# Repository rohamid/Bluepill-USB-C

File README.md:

# STM32F103 Bluepill USB C #
STM32F103 Bluepill PCB with USB C and castellated PCB.

## Warning ##
After finished and ordering from `JLCPCB` I spotted a mistake that I swapped USB D- with D+ and vice versa.

## Problem fixed ##
* [ ] Fixing swapped D- D+ USB trace

## Bluepill USB C PCB ##

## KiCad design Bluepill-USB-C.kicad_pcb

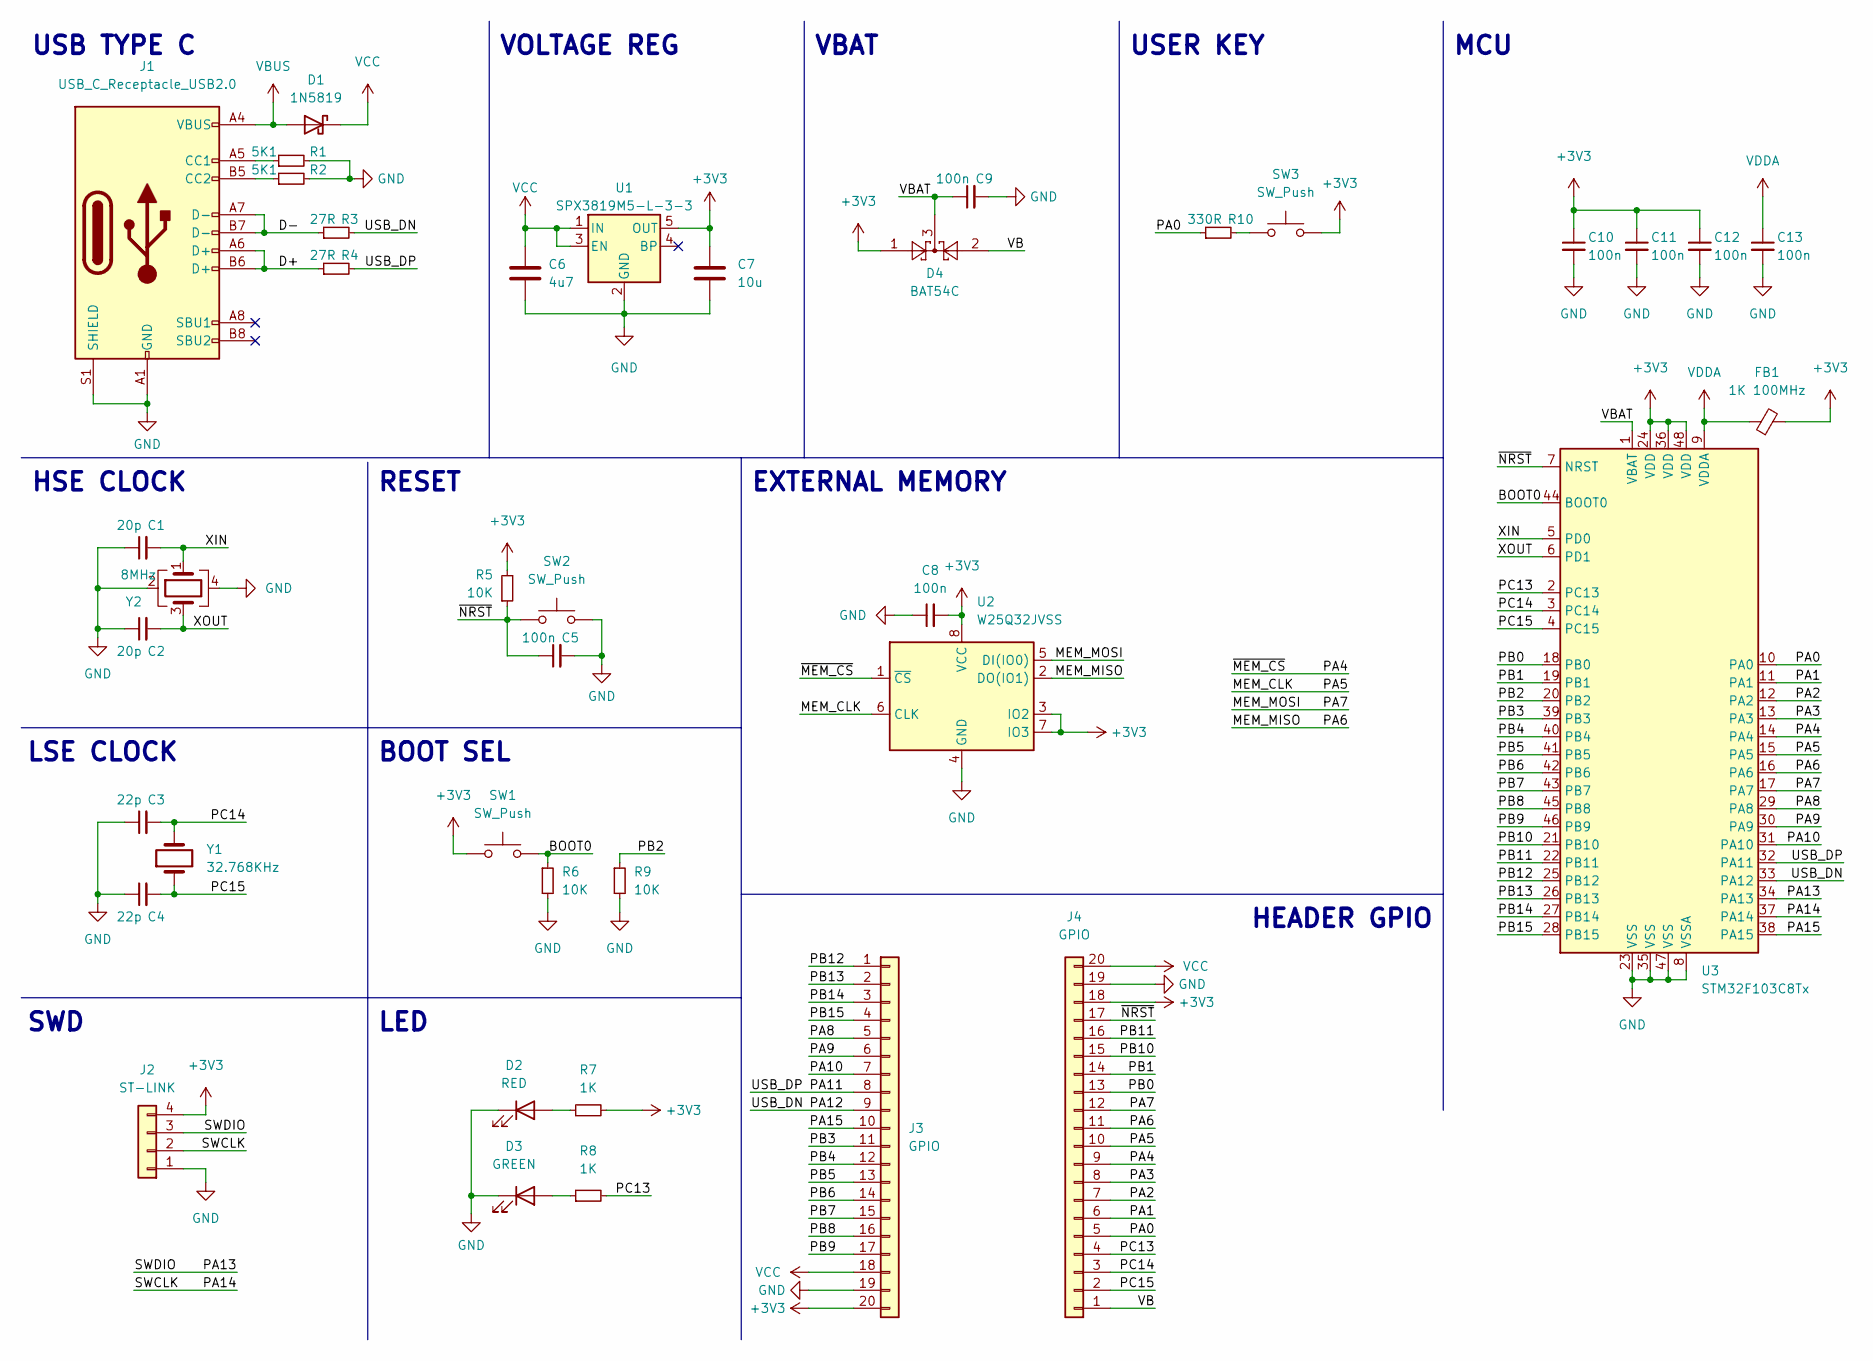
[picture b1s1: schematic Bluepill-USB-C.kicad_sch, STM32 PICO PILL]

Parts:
C1, C2: 20p; C_0402_1005Metric; LCSC Part Number C1554
C3, C4: 22p; C_0402_1005Metric; LCSC Part Number C1555
C5, C8, C9, C10, C11, C12, C13: 100n; C_0402_1005Metric; LCSC Part Number C307331
C6: 4u7; C_0603_1608Metric; LCSC Part Number C19666
C7: 10u; C_0603_1608Metric; LCSC Part Number C19702
D1: 1N5819; D_SOD-323; LCSC Part Number C191023
D2: RED; LED_0805_2012Metric; LCSC Part Number C84256
D3: GREEN; LED_0805_2012Metric; LCSC Part Number C34499
D4: BAT54C; SOT-23; LCSC Part Number C37704
FB1: 1K 100MHz; L_0402_1005Metric; LCSC Part Number C76884
J1: USB_C_Receptacle_USB2.0; USB_C_Receptacle_G-Switch_GT-USB-7010ASV
J2: ST-LINK; castellated_header_4p
J3, J4: GPIO; castellated_20p
R1, R2: 5K1; R_0402_1005Metric; LCSC Part Number C25905
R3, R4: 27R; R_0402_1005Metric; LCSC Part Number C25092
R5, R6, R9: 10K; R_0402_1005Metric; LCSC Part Number C25744
R7, R8: 1K; R_0402_1005Metric; LCSC Part Number C11702
R10: 330R; R_0402_1005Metric; LCSC Part Number C25104
SW1, SW2, SW3: SW_Push; SW_Push_1P1T_NO_CK_KMR2; LCSC Part Number C127488
U1: SPX3819M5-L-3-3; SOT-23-5; LCSC Part Number C9055
U2: W25Q32JVSS; SOIC-8_5.23x5.23mm_P1.27mm; LCSC Part Number C97521
U3: STM32F103C8Tx; LQFP-48_7x7mm_P0.5mm; LCSC Part Number C8734
Y1: 32.768KHz; Crystal_SMD_3215-2Pin_3.2x1.5mm; LCSC Part Number C93232
Y2: 8MHz; Crystal_SMD_3225-4Pin_3.2x2.5mm; LCSC Part Number C253723

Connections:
+3V3: C7.1, C8.2, C10.1, C11.1, C12.1, D4.1, FB1.2, J2.4, J3.20, J4.18, R5.2, R7.2, SW1.1, SW3.2, U1.5 (OUT), U2.3 (IO2), U2.7 (IO3), U2.8 (VCC), U3.24 (VDD), U3.36 (VDD), U3.48 (VDD)
/BOOT0: R6.1, SW1.2, U3.44 (BOOT0)
/D+: J1.A6 (D+), J1.B6 (D+), R4.1
/D-: J1.A7 (D-), J1.B7 (D-), R3.1
/MEM_CLK: J4.10, U2.6 (CLK), U3.15 (PA5)
/MEM_MISO: J4.11, U2.2 (DO(IO1)), U3.16 (PA6)
/MEM_MOSI: J4.12, U2.5 (DI(IO0)), U3.17 (PA7)
/PA0: J4.5, R10.1, U3.10 (PA0)
/PA1: J4.6, U3.11 (PA1)
/PA2: J4.7, U3.12 (PA2)
/PA3: J4.8, U3.13 (PA3)
/PA4: J4.9, U2.1 (~CS), U3.14 (PA4)
/PA8: J3.5, U3.29 (PA8)
/PA9: J3.6, U3.30 (PA9)
/PA10: J3.7, U3.31 (PA10)
/PA11: J3.8, R4.2, U3.32 (PA11)
/PA12: J3.9, R3.2, U3.33 (PA12)
/PA13: J2.3, U3.34 (PA13)
/PA14: J2.2, U3.37 (PA14)
/PA15: J3.10, U3.38 (PA15)
/PB0: J4.13, U3.18 (PB0)
/PB1: J4.14, U3.19 (PB1)
/PB2: R9.1, U3.20 (PB2)
/PB3: J3.11, U3.39 (PB3)
/PB4: J3.12, U3.40 (PB4)
/PB5: J3.13, U3.41 (PB5)
/PB6: J3.14, U3.42 (PB6)
/PB7: J3.15, U3.43 (PB7)
/PB8: J3.16, U3.45 (PB8)
/PB9: J3.17, U3.46 (PB9)
/PB10: J4.15, U3.21 (PB10)
/PB11: J4.16, U3.22 (PB11)
/PB12: J3.1, U3.25 (PB12)
/PB13: J3.2, U3.26 (PB13)
/PB14: J3.3, U3.27 (PB14)
/PB15: J3.4, U3.28 (PB15)
/PC13: J4.4, R8.2, U3.2 (PC13)
/PC14: C3.2, J4.3, U3.3 (PC14), Y1.2
/PC15: C4.2, J4.2, U3.4 (PC15), Y1.1
/VB: D4.2, J4.1
/VBAT: C9.1, D4.3, U3.1 (VBAT)
/XIN: C1.2, U3.5 (PD0), Y2.1
/XOUT: C2.2, U3.6 (PD1), Y2.3
/~NRST: C5.1, J4.17, R5.1, SW2.1, U3.7 (NRST)
GND: C1.1, C2.1, C3.1, C4.1, C5.2, C6.2, C7.2, C8.1, C9.2, C10.2, C11.2, C12.2, C13.2, D2.1 (K), D3.1 (K), J1.A1 (GND), J1.A12 (GND), J1.B1 (GND), J1.B12 (GND), J1.S1 (SHIELD), J2.1, J3.19, J4.19, R1.2, R2.2, R6.2, R9.2, SW2.2, U1.2 (GND), U2.4 (GND), U3.8 (VSSA), U3.23 (VSS), U3.35 (VSS), U3.47 (VSS), Y2.2, Y2.4
unnamed: D2.2 (A), R7.1
unnamed: D3.2 (A), R8.1
unnamed: J1.A5 (CC1), R1.1
unnamed: J1.B5 (CC2), R2.1
unnamed: R10.2, SW3.1
VBUS: D1.2 (A), J1.A4 (VBUS), J1.A9 (VBUS), J1.B4 (VBUS), J1.B9 (VBUS)
VCC: C6.1, D1.1 (K), J3.18, J4.20, U1.1 (IN), U1.3 (EN)
VDDA: C13.1, FB1.1, U3.9 (VDDA)

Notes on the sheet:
MCU
RESET
BOOT SEL
HEADER GPIO
EXTERNAL MEMORY
VOLTAGE REG
VBAT
SWD
USB TYPE C
LED
HSE CLOCK
USER KEY
LSE CLOCK

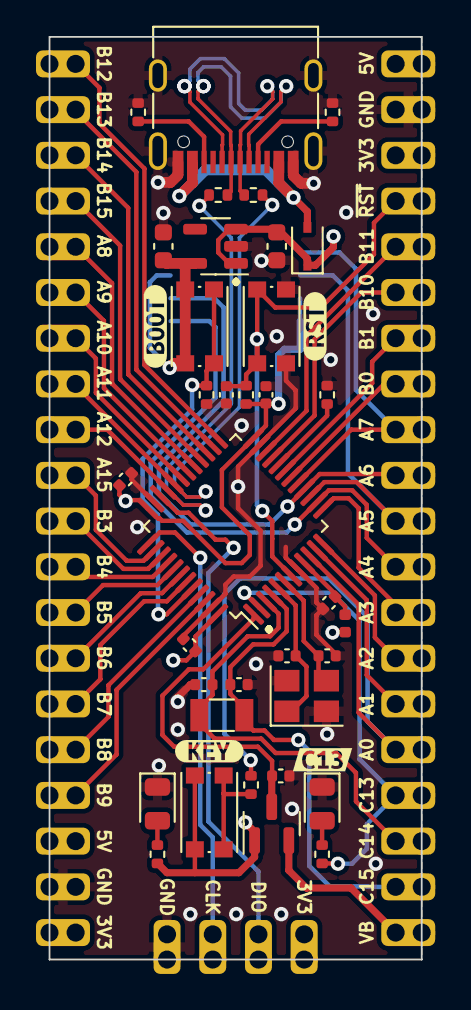
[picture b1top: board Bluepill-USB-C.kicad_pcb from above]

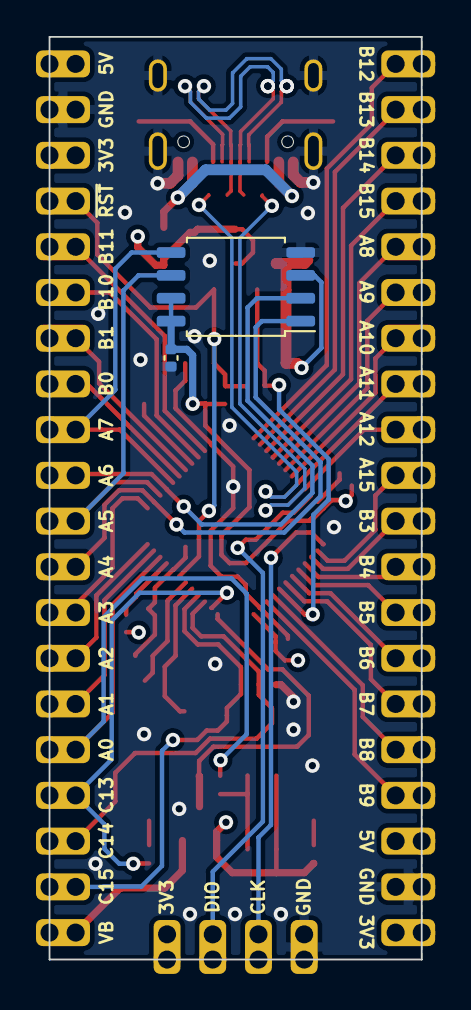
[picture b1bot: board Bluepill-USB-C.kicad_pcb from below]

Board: 4 copper layers, 20.7 x 51.3 mm, 44 parts (2 on the bottom side), 53 nets.

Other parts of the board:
kibuzzard-63FDC3E6: G***; kibuzzard-63FDC3E6
kibuzzard-63FDC36C: G***; kibuzzard-63FDC36C
kibuzzard-63FDC37C: G***; kibuzzard-63FDC37C
kibuzzard-63FDCD3E: G***; kibuzzard-63FDCD3E

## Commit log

2024-02-23 modified : README
